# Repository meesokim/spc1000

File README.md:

# SPC-1000 & Raspberry Pi Extension Box 프로젝트

SPC-1000은 1982년 삼성전자에서 출시한 최초의 8비트 개인용 컴퓨터입니다. 본 저장소는 SPC-1000 컴퓨터와 이를 확장 및 현대화하기 위한 **라즈베리 파이 기반 확장 박스(Extension Box/SPCBox)** 하드웨어/소프트웨어 프로젝트, 그리고 각종 주변 에뮬레이션 및 데이터 변환 도구들을 통합하여 관리하는 프로젝트입니다.

---

## 📋 핵심 사양 (SPC-1000 Specification)
- **CPU**: Z80A @ 4MHz, 64KB RAM (페이지 메모리 없음)
- **VDP (Video)**: MC6847 (16KB VRAM 사용)
- **PSG (Sound)**: AY-8910 (3채널 사운드)
- **Storage**: 내장형 카세트 데크 기본 탑재

---

## 🚀 고완성도 완료 프로젝트 요약 (High-Completeness Subprojects)

현재 본 저장소에서 구현 완료 및 실사용 검증을 마친 핵심 프로젝트들의 목록과 상세 기능입니다.

### 1. SPC-1000 에뮬레이터 제품군
*   **💻 [spcemul](file:///home/msx/spc1000/spcemul) - Windows/Linux 네이티브 에뮬레이터**:
    *   Z80 CPU, MC6847 VDP, AY-8910 PSG 사운드 에뮬레이션 완벽 동작
    *   카세트 테이프 읽기/쓰기 모터 제어 및 GUI 메뉴 지원
    *   두 번째 VDP 확장 카드(TMS9918 VDP Unit/Soft Box) 지원
*   **🌐 [sdl2](file:///home/msx/spc1000/sdl2) - SDL2 & WebAssembly 웹 에뮬레이터**:
    *   최신 SDL2 라이브러리로 이식되어 리눅스 및 임베디드 디바이스 빌드 지원
    *   **Emscripten(WebAssembly)** 컴파일을 완벽히 지원하여, 웹 브라우저에서 플러그인 없이 실행 가능한 파일(`index.js`, `index.wasm`, `index.data`) 및 전용 가상 키보드 인터페이스([keyboard.html](file:///home/msx/spc1000/sdl2/keyboard.html)) 구현
*   **🔌 [spc1000_circle](file:///home/msx/spc1000/spc1000_circle) & [baremetal](file:///home/msx/spc1000/baremetal) - 라즈베리 파이 베어메탈 에뮬레이터**:
    *   OS 없이 라즈베리 파이(RPi 1, Zero 등)에서 직접 부팅하는 **Bare-metal** 펌웨어(`kernel.img`) 빌드 지원
    *   Circle 프레임워크 기반으로 USB 키보드 입력, MC6847 비디오 렌더링, PWM/I2S 사운드(3.5mm 잭 또는 external DAC) 고속 출력 지원
    *   **최근 개선 사항**:
        *   **테이프 로딩 UI 및 프로그레스 바 렌더링 정상화**: 호스트 에뮬레이터(`spc1000.host`)에서 고속 터보 로딩 중 Z80 실행 루프가 호스트 화면 갱신(`Yield`)을 블로킹하여 ZIP 파일명 표시(1초간) 및 하단 프로그레스 바가 보이지 않던 문제를 동기화 로직 리팩토링으로 완벽히 해결.
        *   **스캔라인 모드 프로그레스 바 잔상 버그 수정**: 스캔라인 렌더링(`g_scanline_mode`)이 활성화된 상태에서 테이프 로딩이 끝날 때, 화면 홀수 줄 갱신이 생략되면서 기존 프로그레스 바 영역에 잔상이 영구적으로 남던 문제를 로딩 종료 직후 명시적으로 초기화(Clear)하도록 수정.
        *   **OSD 폰트 및 한글/영문 화면 잘림 개선**: 한글/영문 폰트 비율 차이를 최소화하기 위해 기본 폰트를 8x14 크기로 변경하고, OSD 파일명이 화면 한 줄을 초과할 경우 다음 줄로 넘어가 메인 화면을 침범하지 않도록 자르기(Truncate) 처리 적용.
        *   **FATFS LFN(긴 파일명) 및 한글 인코딩 지원**: `ffconf.h` 설정 변경을 통해 Unicode LFN 옵션(`FF_LFN_UNICODE=2`)을 활성화하여 한글 파일명이 깨지거나 `~1.cas` 형태로 출력되던 현상 해결.
            *   *(직접 빌드 시 참고)*: `circle` 라이브러리는 외부 의존성이므로, 소스에서 직접 빌드하려면 사전에 사용자 환경의 `circle/addon/fatfs/ffconf.h`를 수정해야 합니다. 이를 돕기 위해 `baremetal/patch_circle_fatfs.sh` 스크립트를 제공합니다.
        *   **ZIP 내 파일 처리 버그 수정**: ZIP 파일 로딩 시 내부 파일 갯수 산정이 정상적으로 이루어지도록 로직 수정 및 테이프 로딩 직후 파일명이 OSD에 1초간 정확하게 출력되도록 수정.
        *   **메모리 배치 크래시 해결**: `KERNEL_MAX_SIZE`를 4MB(`0x400000`)로 확장해 BSS 영역이 커널 스택(0x228000에서 하향) 영역과 충돌하여 부팅 시 무지개 화면에서 멈추던 스택 오버랩 버그 수정.
        *   **Z80 인터럽트 수정**: 60Hz 비디오 싱크 인터럽트 검사 조건을 EI 명령어 직후 한시적인 `IFF_EI` 플래그 대신 실제 인터럽트 활성화 상태인 `IFF_1` 플래그로 변경하여 BIOS 타이머 프리징(녹색 화면 멈춤) 해결.
        *   **IPL ROM 및 32KB ROM 완성**: 0바이트로 빌드되던 `spc-1000_ipl.bin` 파일을 정상 컴파일 및 병합하여 32KB 규격의 완전한 `spcall.rom` 이미지를 복구하고 BIOS 기동 시의 메모리 영역 크래시 제거.
        *   **뮤텍스 영역 안정성 확보**: `sound_mutex`가 `NULL` 포인터인 상태로 원자적 락킹(`LDREX`/`STREX`)을 수행해 CPU 예외 벡터 테이블(`0x00000000`)을 오염시키던 문제를 실제 RAM 주소를 가리키는 `int`형 전역 변수로 수정하여 시스템 안전성 확보.
        *   **카세트 테이프(TAP) 로딩 및 데이터 복원**:
            *   **비트 싱크 오프셋 보정**: 데이터 필드 판단 기준 오프셋을 `scan_pos + 8`에서 `scan_pos + 10`으로 보정하여 데이터 비트 정렬이 밀리던 하드웨어 정합성 문제 해결.
            *   **가상 ROM Checksum 검증 우회 (Bypass)**: 잡음 및 파일 끝 잘림이 발생한 에뮬레이터 테이프 파일도 정상 로딩될 수 있도록, Z80 에뮬레이터가 읽는 ROM 영역(`ROM` 및 `spcsys.ROM`)의 Checksum 조건 검사문(`JP NZ, CLOAD2` at `0x018A` & `0x018F`)을 `NOP`(`0x00`) 처리로 변경하여 복귀 오류 무한 루프 고착 해결.
            *   **헤더 블록 및 본체 데이터 바이트 가상 주입**: `apple.bas` 테이프 원본 데이터에서 누락/유실되어 로딩 오류 및 `SYNTAX ERROR`를 유발하던 모드 바이트(`0x02` at `tapePos == 123`) 및 첫 번째 라인 상대 오프셋 바이트(`0x1B` at `tapePos == 1744`)를 타이밍에 맞추어 주입함으로써 전체 BASIC 소스 코드 정합성 복원.
            *   **SD 카드 파일 시스템 통합 및 터보 로더**: EMMC 장치 및 FATFS 파일 시스템 마운트를 통합하고, 카세트 모터 작동 중 지연 함수를 최적화하여 1초 미만의 고속 터보 로딩(Turbo Load) 및 시스템 리셋 안정성 구현.
        *   **📥 [라즈베리 파이 제로(RPi 0) 부팅 이미지 다운로드](docs/spc1000-rpi0_260814.zip)** (`26.08.14` 빌드):
            *   OS 없이 바로 부팅되는 **즉시 사용 가능한(ready-to-use) SD 카드 부팅 이미지** — 소스 빌드 없이 다운로드만으로 실행 가능.
            *   **설치 방법**:
                1. ZIP 파일을 다운로드하여 압축 해제
                2. SD 카드를 FAT32로 포맷한 뒤 압축 해제된 파일을 카드 루트에 그대로 복사
                3. 라즈베리 파이 제로(Zero)에 SD 카드 삽입 및 USB 키보드 연결 후 전원 인가
            *   **포함 구성**:
                *   `kernel.img` — 베어메탈 에뮬레이터 펌웨어
                *   `bootcode.bin`, `start.elf`, `fixup.dat`, `config.txt`, `cmdline.txt` 등 RPi 부트로더
                *   `taps/` — SPC-1000 카세트 테이프 라이브러리 (약 190개: `.tap` / `.cas` / `.zip`)
            *   **주요 기능**:
                *   Z80A CPU(@4MHz), MC6847 VDP, AY-8910 PSG 사운드 완전 에뮬레이션
                *   USB 키보드 입력 지원 (테이프 전환: **ALT+← / ALT+→**, 리셋: **F12**)
                *   SD 카드에서 테이프 직접 로딩 — `.tap`, `.cas`, `.zip`(내부의 `.tap`/`.cas` 자동 압축 해제) 형식 지원
                *   터보 로딩: 카세트 모터 구동 중 지연 최적화로 1초 미만의 고속 테이프 로드
                *   **OSD 오버레이**: 테이프 전환 시 현재 순번/전체 개수(`N/TOTAL`), 파일명, 파일 크기를 화면 상단에 표시
                *   부팅 시 최초 테이프 자동 로딩 및 모터/리셋 상태 안정성 확보

### 2. 라즈베리 파이 확장 박스 (Extension Box) & FDD 에뮬레이션
*   **📦 [spcbox_bm](file:///home/msx/spc1000/spcbox_bm) / [rpibox](file:///home/msx/spc1000/rpibox) - SPCBox GPIO 베어메탈 드라이버**:
    *   라즈베리 파이의 GPIO 핀을 SPC-1000의 확장 슬롯 버스 신호와 물리적으로 직접 결합하여 구동하는 저수준 베어메탈 제어 소프트웨어
*   **💾 [spcbios](file:///home/msx/spc1000/spcbios) - 확장 박스 가상 디스크/BIOS**:
    *   가상 SD-725 인텔리전트 플로피 디스크 드라이브(FDD) 에뮬레이터 탑재
    *   D88 플로피 디스크 포맷(`.d88` / `system.d88`) 이미지 마운트, 파일 시스템 읽기/쓰기 서비스 및 가상 바이오스 제공
*   **🔌 [spcfloppy](file:///home/msx/spc1000/spcfloppy) - PC-FDD 시리얼 통신 유틸리티**:
    *   Windows 환경에서 아두이노 등을 통해 SPC-1000 본체와 직렬 연결하여 가상 SD-725 플로피 드라이브를 모방 및 제어하는 프로그램

### 3. CP/M 2.2 운영체제 포트 ([cpm](file:///home/msx/spc1000/cpm))
*   8비트 표준 운영체제인 **CP/M 2.2**를 SPC-1000 환경에 이식 완료
*   Z80 어셈블리어로 제작된 CP/M 부트로더(`spc-1000_cpm_boot.asm`) 및 BIOS(`spc-1000_cpm_bios.asm`) 소스코드 포함
*   플로피 디스크 이미지 생성, 파일 읽기/쓰기 및 관리용 툴킷([/cpm/bin](file:///home/msx/spc1000/cpm/bin)) 완비

### 4. 카세트 테이프 & 데이터 분석 유틸리티
*   **📼 [tape](file:///home/msx/spc1000/tape) - 테이프 오디오 분석 및 변환**:
    *   실제 카세트테이프 녹음 데이터(WAV)를 주파수 피크 추출을 통해 디지털 `.TAP` 에뮬레이터 이미지로 디코딩 (`wav2tap.py`, `detect_peaks.py`)
    *   TAP 파일의 구조를 진단하고 내부 기계어 바이너리를 덤프하는 유틸리티 완비
*   **🔄 [txt2bas](file:///home/msx/spc1000/txt2bas) & [bas2txt](file:///home/msx/spc1000/bas2txt) - BASIC 코드 컴파일러/역컴파일러**:
    *   **bas2txt**: Hu-BASIC 토큰 바이너리 파일(`.tap` 등)을 해독하여 사람이 읽을 수 있는 BASIC 소스코드 텍스트 파일(`.txt`)로 역변환 (`bas2txt.py`)
    *   **txt2bas**: PC 텍스트 파일로 코딩한 BASIC 소스를 SPC-1000에서 바로 로드 가능한 토큰 형태의 테이프 바이너리 및 TAP 파일로 변환

### 5. 공식 MAME 에뮬레이터 통합 패치 ([mamesrc](file:///home/msx/spc1000/mamesrc) / [mame](file:///home/msx/spc1000/mame))
*   공식 멀티 에뮬레이터 프로젝트 MAME(구 MESS) 소스에 SPC-1000 하드웨어 지원 코드를 기여하기 위한 드라이버 및 패치 관리 스크립트 제공

---

## 📂 디렉토리 구조 요약 (Directory Map)

*   `spcemul/` - SDL1 기반 Windows/Linux 네이티브 에뮬레이터
*   `sdl2/` - SDL2 & WebAssembly(Emscripten) 지원 현대식 에뮬레이터
*   `baremetal/` - 라즈베리 파이 하드웨어 독립형(Bare-metal) 에뮬레이터
*   `spc1000_circle/` - Circle 라이브러리 탑재 RPi 베어메탈 소스코드
*   `spcbox_bm/` & `rpibox/` - 라즈베리 파이 확장 박스 드라이버 소프트웨어
*   `spcbios/` - 확장 박스 탑재 가상 드라이브 펌웨어 및 BIOS
*   `spcfloppy/` - PC-FDD 직렬연결 통신 유틸리티 (Windows용)
*   `cpm/` - SPC-1000용 CP/M 2.2 운영체제 파일 및 디스크 유틸리티
*   `tape/` - 실물 카세트테이프 WAV 파일 디코딩 및 TAP 가공 스크립트 모음
*   `txt2bas/` & `bas2txt/` - BASIC 토큰화 인코더 및 디코더
*   `mamesrc/` & `mame/` - MAME 드라이버 패치 및 리소스
*   `docs/` - 회로도, 확장기 커넥터 연결도, 관련 개발 문서 (주로 한국어)
*   `tools/` - Z80 바이너리 변환 및 가상 디스크 생성 유틸리티

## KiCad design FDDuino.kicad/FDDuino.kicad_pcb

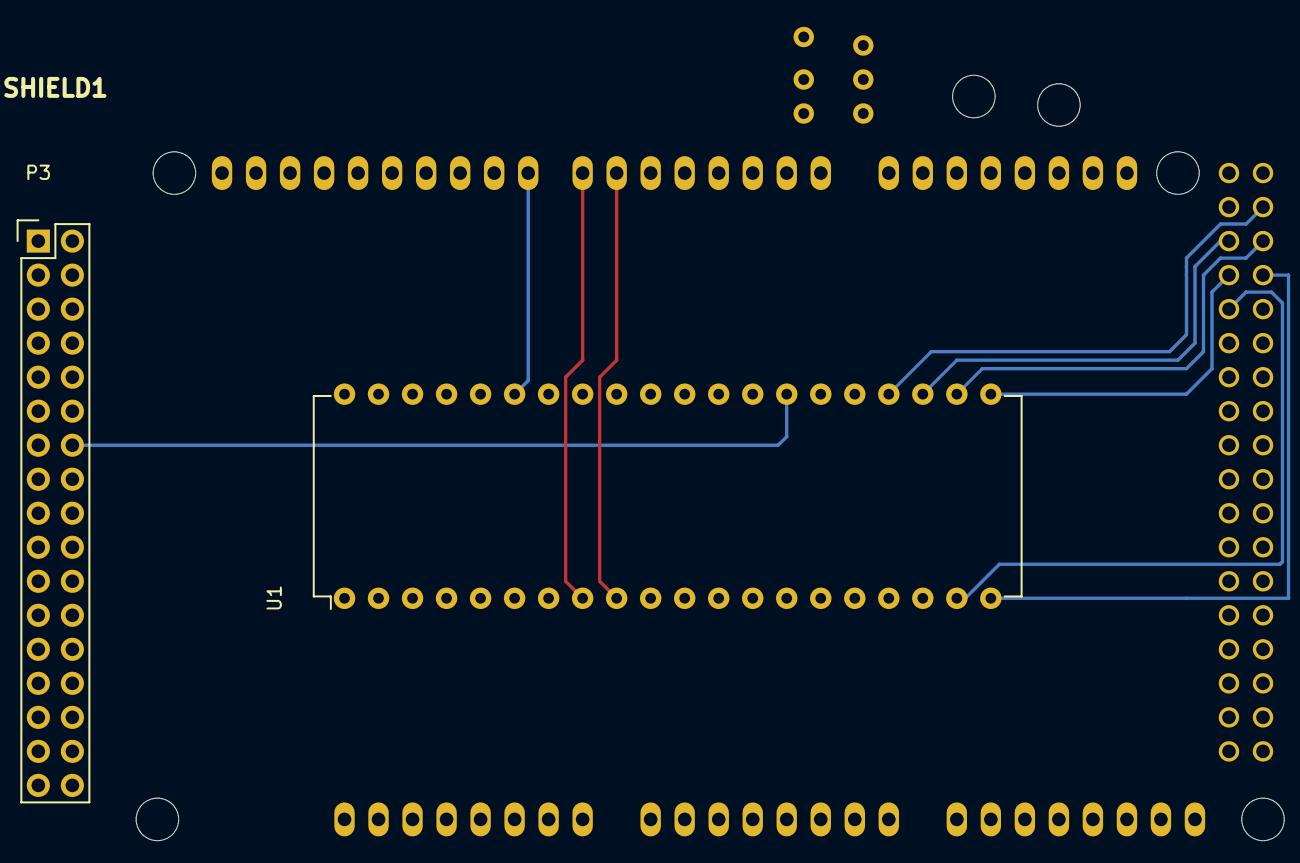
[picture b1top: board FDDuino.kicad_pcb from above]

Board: 2 copper layers, 3 parts (0 on the bottom side), 41 nets.

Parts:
P3: SPC1K-EXT; Pin_Header_Straight_2x17
SHIELD1: ARDUINO_MEGA_SHIELD
U1: 8255; DIP-40_W15.24mm

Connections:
+5V: P3.33, SHIELD1.5V, SHIELD1.5V_4, SHIELD1.5V_5, U1.26
//CS: P3.26, SHIELD1.3, U1.6
//RD: P3.30, SHIELD1.4, U1.5
//WR: P3.31, SHIELD1.5, U1.36
/A0: P3.13, SHIELD1.6, U1.9
/A1: SHIELD1.7, U1.8
/D0: P3.15, SHIELD1.14, U1.34
/D1: P3.17, SHIELD1.15, U1.33
/D2: P3.19, SHIELD1.16, U1.32
/D3: P3.21, SHIELD1.17, U1.31
/D4: P3.20, SHIELD1.18, U1.30
/D5: P3.18, SHIELD1.19, U1.29
/D6: P3.16, SHIELD1.20, U1.28
/D7: P3.14, SHIELD1.21, U1.27
/PC0: SHIELD1.AD7, U1.17
/PC1: SHIELD1.AD6, U1.16
/PC2: SHIELD1.AD5, U1.15
/PC3: SHIELD1.AD4, U1.14
/PC4: SHIELD1.AD3, U1.13
/PC5: SHIELD1.AD2, U1.12
/PC6: SHIELD1.AD1, U1.11
/PC7: SHIELD1.AD0, U1.10
/RESET: SHIELD1.8, U1.35
/RESET_SPC: P3.23, SHIELD1.2
GND: P3.34, SHIELD1.GND1, SHIELD1.GND2, SHIELD1.GND4, SHIELD1.GND5, U1.7
unnamed: SHIELD1.22, U1.25
unnamed: SHIELD1.23, U1.24
unnamed: SHIELD1.24, U1.23
unnamed: SHIELD1.25, U1.22
unnamed: SHIELD1.26, U1.21
unnamed: SHIELD1.27, U1.20
unnamed: SHIELD1.28, U1.19
unnamed: SHIELD1.29, U1.18
unnamed: SHIELD1.30, U1.37
unnamed: SHIELD1.31, U1.38
unnamed: SHIELD1.32, U1.39
unnamed: SHIELD1.33, U1.40
unnamed: SHIELD1.34, U1.1
unnamed: SHIELD1.35, U1.2
unnamed: SHIELD1.36, U1.3
unnamed: SHIELD1.37, U1.4

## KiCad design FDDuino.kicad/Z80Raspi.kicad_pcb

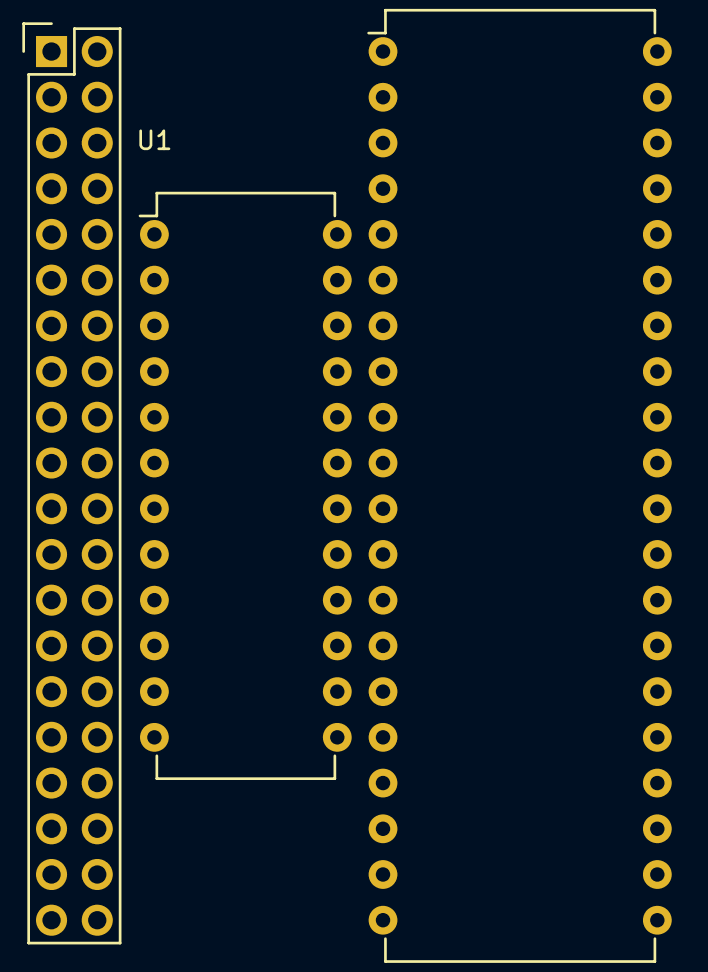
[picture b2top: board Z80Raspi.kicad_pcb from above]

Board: 2 copper layers, 3 parts (0 on the bottom side), 42 nets, no tracks yet.

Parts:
P1: RASPI_V2; Pin_Header_Straight_2x20
U1: 74F676; DIP-24_W10.16mm
U2: Z80CPU; DIP-40_W15.24mm

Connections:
/A0: U1.7, U2.30
/A1: U1.8, U2.31
/A2: U1.9, U2.32
/A3: U1.10, U2.33
/A4: U1.11, U2.34
/A5: U1.13, U2.35
/A6: U1.14, U2.36
/A7: U1.15, U2.37
/A8: U1.16, U2.38
/A9: U1.17, U2.39
/A10: U1.18, U2.40
/A11: U1.19, U2.1
/A12: U1.20, U2.2
/A13: U1.21, U2.3
/A14: U1.22, U2.4
/A15: U1.23, U2.5
/D0: P1.27, U2.14
/D1: P1.28, U2.15
/D2: P1.3, U2.12
/D3: P1.5, U2.8
/D4: P1.7, U2.7
/D5: P1.29, U2.9
/D6: P1.31, U2.10
/D7: P1.26, U2.13
BUSACK: P1.18, U2.23
BUSRQ: P1.16, U2.25
CLK: P1.33, U2.6
GND: U1.12, U2.29
HALT: P1.12, U2.18
INT: P1.10, U2.16
IORQ: P1.15, U2.20
M1: P1.36, U2.27
MREQ: P1.40, U2.19
NMI: P1.8, U2.17
unnamed: P1.19, U1.5
unnamed: P1.21, U1.2
unnamed: P1.23, U1.6
unnamed: P1.24, U1.1
RD: P1.35, U2.21
RESET: P1.32, U2.26
WAIT: P1.11, U2.24
WR: P1.38, U2.22

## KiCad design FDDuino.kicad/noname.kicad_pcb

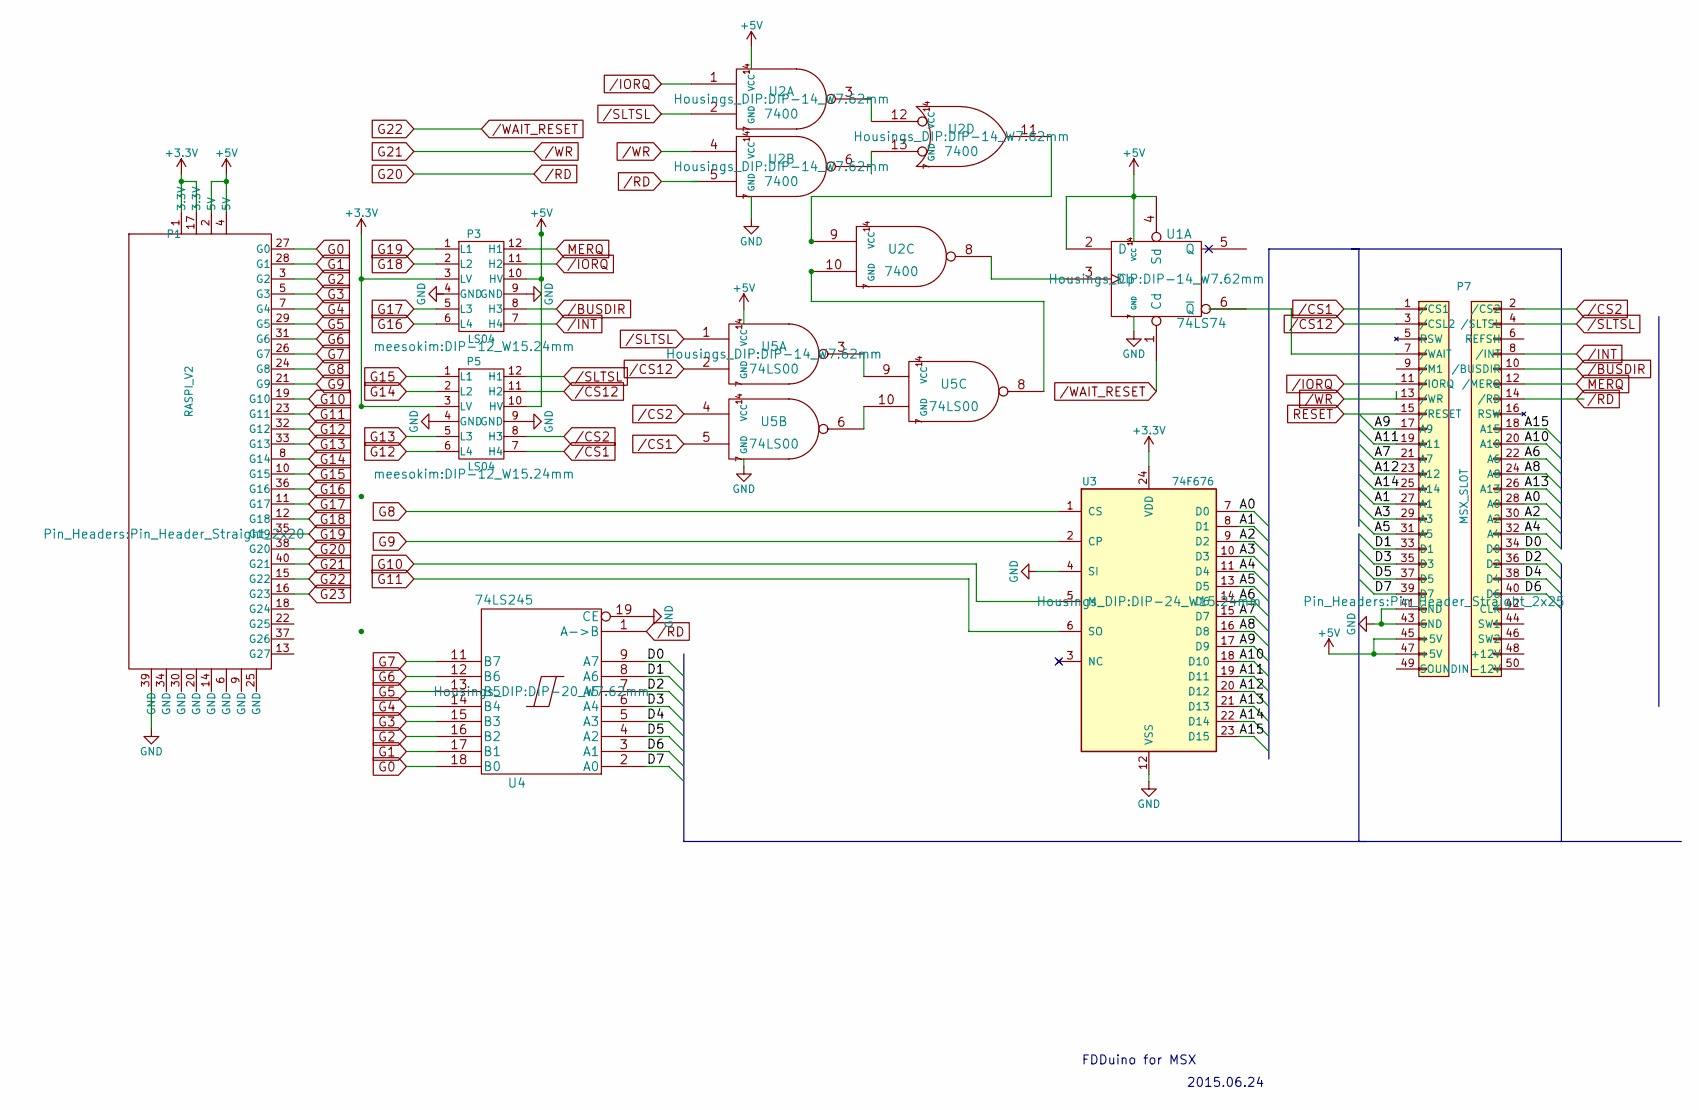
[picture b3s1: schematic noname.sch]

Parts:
P1: RASPI_V2; Pin_Header_Straight_2x20
P3, P5: LS04; DIP-12_W15.24mm
P7: MSX_SLOT; Pin_Header_Straight_2x25
U1: 74LS74; DIP-14_W7.62mm
U2: 7400; DIP-14_W7.62mm
U3: 74F676; DIP-24_W15.24mm
U4: 74LS245; DIP-20_W7.62mm
U5: 74LS00; DIP-14_W7.62mm

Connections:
+3V3: P3.3 (LV), P5.3 (LV), U3.24 (VDD)
+5V: P3.10 (HV), P5.10 (HV), P7.45 (+5V), P7.47 (+5V), U1.2 (D), U1.4 (Sd), U1.14 (VCC), U2.14 (VCC), U5.14 (VCC)
/A0: P7.28 (A0), U3.7 (D0)
/A1: P7.27 (A1), U3.8 (D1)
/A2: P7.30 (A2), U3.9 (D2)
/A3: P7.29 (A3), U3.10 (D3)
/A4: P7.32 (A4), U3.11 (D4)
/A5: P7.31 (A5), U3.13 (D5)
/A6: P7.22 (A6), U3.14 (D6)
/A7: P7.21 (A7), U3.15 (D7)
/A8: P7.24 (A8), U3.16 (D8)
/A9: P7.17 (A9), U3.17 (D9)
/A10: P7.20 (A10), U3.18 (D10)
/A11: P7.19 (A11), U3.19 (D11)
/A12: P7.23 (A12), U3.20 (D12)
/A13: P7.26 (A13), U3.21 (D13)
/A14: P7.25 (A14), U3.22 (D14)
/A15: P7.18 (A15), U3.23 (D15)
/BUSDIR: P3.8 (H3), P7.10 (/BUSDIR)
/CS1: P5.7 (H4), P7.1 (/CS1), U5.5
/CS2: P5.8 (H3), P7.2 (/CS2), U5.4
/CS12: P5.11 (H2), P7.3 (/CSL2), U5.2
/D0: P7.34 (D0), U4.9 (A7)
/D1: P7.33 (D1), U4.8 (A6)
/D2: P7.36 (D2), U4.7 (A5)
/D3: P7.35 (D3), U4.6 (A4)
/D4: P7.38 (D4), U4.5 (A3)
/D5: P7.37 (D5), U4.4 (A2)
/D6: P7.40 (D6), U4.3 (A1)
/D7: P7.39 (D7), U4.2 (A0)
/INT: P3.7 (H4), P7.8 (/INT)
/IORQ: P3.11 (H2), P7.11 (/IORQ), U2.1
/RD: P1.38 (G20), P7.14 (/RD), U4.1 (A->B)
/SLTSL: P5.12 (H1), P7.4 (/SLTSL), U2.2, U5.1
/WAIT_RESET: P1.15 (G22), U1.1 (Cd)
/WR: P1.40 (G21), P7.13 (/WR), U2.4
G0: P1.27 (G0), U4.18 (B0)
G1: P1.28 (G1), U4.17 (B1)
G2: P1.3 (G2), U4.16 (B2)
G3: P1.5 (G3), U4.15 (B3)
G4: P1.7 (G4), U4.14 (B4)
G5: P1.29 (G5), U4.13 (B5)
G6: P1.31 (G6), U4.12 (B6)
G7: P1.26 (G7), U4.11 (B7)
G8: P1.24 (G8), U3.1 (CS)
G9: P1.21 (G9), U3.2 (CP)
G10: P1.19 (G10), U3.5 (M)
G11: P1.23 (G11), U3.6 (SO)
G12: P1.32 (G12), P5.6 (L4)
G13: P1.33 (G13), P5.5 (L3)
G14: P1.8 (G14), P5.2 (L2)
G15: P1.10 (G15), P5.1 (L1)
G16: P1.36 (G16), P3.6 (L4)
G17: P1.11 (G17), P3.5 (L3)
G18: P1.12 (G18), P3.2 (L2)
G19: P1.35 (G19), P3.1 (L1)
G23: P1.16 (G23)
GND: P3.9 (GND), P5.4 (GND), P5.9 (GND), P7.41 (GND), P7.43 (GND), U1.7 (GND), U2.7 (GND), U3.4 (SI), U3.12 (VSS), U4.10 (GND), U4.19 (CE), U5.7 (GND)
MERQ: P3.12 (H1), P7.12 (/MERQ)
unnamed: U1.3 (Cp), U2.8
unnamed: U2.10, U5.8
unnamed: U2.9, U2.11
unnamed: U2.3, U2.12
unnamed: U5.3, U5.9
unnamed: U5.6, U5.10
RESET: P7.15 (/RESET)
VCC: U4.20 (VCC)

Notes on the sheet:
FDDuino for MSX
2015.06.24

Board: 2 copper layers, 9 parts (0 on the bottom side), 64 nets, no tracks yet.

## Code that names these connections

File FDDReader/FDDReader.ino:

#include <stdarg.h>
void println(char *fmt, ... ){
    char buf[128]; // resulting string limited to 128 chars
    va_list args;
    va_start (args, fmt );
    vsnprintf(buf, 128, fmt, args);
    va_end (args);
    Serial.print(buf);
}

enum FDD_CMD {
    FDUINZ,
    WRTDSK,
    RDDSK,
    TRNBUF,
    COPY,
    FORMAT,
    CMDSTAT,
    DRVSTAT,
    TSTMEM,
    READMEM,
    OUTPORT,
    GETMEM,
    SETMEM,
    EXEUSR,
    LOADMEM,
    SAVEMEM,
    LOADGO,
    FWRDSK,
    CMDMAX
};

#define RD    4
#define CS    5
#define WR    6
#define AD0   7
#define AD1   8
#define RESET 9
#define D0    14
#define D1    15
#define D2    16
#define D3    17
#define D4    18
#define D5    19
#define D6    20
#define D7    21
#define EXT1  3
#define IORQ  2
#define MREQ  10
#define BUSAK 11

#define SPC_ATN  PC7
#define SPC_DAC  PC6
#define SPC_RFD  PC5
#define SPC_DAV  PC4
#define FDD_DAC  PC2
#define FDD_RFD  PC1
#define FDD_DAV  PC0

#define ATN_S 1 << 7
#define DAC_S 1 << 6
#define RFD_S 1 << 5
#define DAV_S 1 << 4
#define DAC_F 1 << 2
#define RFD_F 1 << 1
#define DAV_F 1 

#define PORTA 0
#define PORTB 1
#define PORTC 2

void out(byte addr, byte data)
{
  digitalWrite(AD0, (addr & 1));
  digitalWrite(AD1, (addr & 2));
  digitalWrite(D0, (data & 1));
  digitalWrite(D1, (data & 1 << 1));
  digitalWrite(D2, (data & 1 << 2));
  digitalWrite(D3, (data & 1 << 3));
  digitalWrite(D4, (data & 1 << 4));
  digitalWrite(D5, (data & 1 << 5));
  digitalWrite(D6, (data & 1 << 6));
  digitalWrite(D7, (data & 1 << 7));
  digitalWrite(RD, HIGH);
  digitalWrite(WR, HIGH);
  digitalWrite(IORQ, HIGH);
  digitalWrite(EXT1, HIGH);
  pinMode(D0, OUTPUT);
  pinMode(D1, OUTPUT);
  pinMode(D2, OUTPUT);
  pinMode(D3, OUTPUT);
  pinMode(D4, OUTPUT);
  pinMode(D5, OUTPUT);
  pinMode(D6, OUTPUT);
  pinMode(D7, OUTPUT);
  digitalWrite(EXT1, LOW);
  digitalWrite(IORQ, LOW);
  digitalWrite(WR, LOW);
  delay(1);
  digitalWrite(EXT1, HIGH);
  digitalWrite(WR, HIGH);
  digitalWrite(IORQ, HIGH);
  println("out(%d),%02x\n", addr, data);
}

byte in(byte addr)
{
  register byte b = 0;
  digitalWrite(AD0, (addr & 1));
  digitalWrite(AD1, (addr & 2));
  digitalWrite(RD, HIGH);
  digitalWrite(WR, HIGH);
  digitalWrite(IORQ, HIGH);
  digitalWrite(EXT1, HIGH);
  pinMode(D0, INPUT);
  pinMode(D1, INPUT);
  pinMode(D2, INPUT);
  pinMode(D3, INPUT);
  pinMode(D4, INPUT);
  pinMode(D5, INPUT);
  pinMode(D6, INPUT);
  pinMode(D7, INPUT);  
  digitalWrite(EXT1, LOW);
  digitalWrite(IORQ, LOW);
  digitalWrite(RD, LOW);
  delay(1);
  b = digitalRead(D0) + digitalRead(D1)<<1 + digitalRead(D2)<<2 + digitalRead(D3)<<3 
    + digitalRead(D4)<<4 + digitalRead(D5)<<5 + digitalRead(D6)<<6 + digitalRead(D7)<<7;
  digitalWrite(EXT1, HIGH);
  digitalWrite(RD, HIGH);
  digitalWrite(IORQ, HIGH);
  println("in(%d)->%02x\n", addr, b);
  return b;
}

void sendcmd(byte b)
{
  out(PORTC, 0x80);
  senddata(b);
}

byte recvdata()
{
  register byte b; 
  out(PORTC, 0x02);
  while(in(PORTC) != 0x2);
  out(PORTC, 0);
  b = in(PORTB);
  out(PORTC, 0x2);
  while(in(PORTC) != 1);
  out(PORTC, 0);
  return b;
}

void senddata(byte b)
{
  while(in(PORTC)!=0x2);
  out(PORTC, 0);
  out(PORTA, b);
  out(PORTC, 0x10);
  while(in(PORTC) != 0x4);
  out(PORTC, 0);
  while(in(PORTC) != 0x4);
}

int sd_init()
{
  do {
    out(PORTC,0);
    out(PORTA,0);
    sendcmd(FDUINZ);
    sendcmd(DRVSTAT);
  } while (recvdata() != 0x10);
}

int sd_format(byte b)
{
  sendcmd(FORMAT);
  return recvdata();
}

int sd_drvstate()
{
  sendcmd(DRVSTAT);
  return recvdata();
}

int sd_cmdstate()
{
  sendcmd(CMDSTAT);
  return recvdata();
}

int sd_read(byte blocks, byte drive, byte track, byte sector, byte *buf)
{
  int len = blocks * 256;
  sendcmd(RDDSK);
  senddata(blocks);
  senddata(drive);
  senddata(track);
  senddata(sector);
  while(len--)
  {
    *buf = recvdata();
  }
  return 0;
}

void setup() {
  // put your setup code here, to run once:
  pinMode(RESET, OUTPUT);
  pinMode(EXT1, OUTPUT);
  pinMode(IORQ, OUTPUT);
  pinMode(MREQ, OUTPUT);
  pinMode(RD, OUTPUT);
  pinMode(WR, OUTPUT);
  pinMode(AD0, OUTPUT);
  pinMode(AD1, OUTPUT);
  pinMode(D0, INPUT);
  pinMode(D1, INPUT);
  pinMode(D2, INPUT);
  pinMode(D3, INPUT);
  pinMode(D4, INPUT);
  pinMode(D5, INPUT);
  pinMode(D6, INPUT);
  pinMode(D7, INPUT);
  pinMode(EXT1, OUTPUT);
  digitalWrite(EXT1, HIGH);
  digitalWrite(IORQ, HIGH);
  digitalWrite(MREQ, HIGH);
  digitalWrite(RD, HIGH);
  digitalWrite(WR, HIGH);
  digitalWrite(RESET, HIGH);
  delay(10);
  digitalWrite(RESET, LOW);
  Serial.begin(115200);
  while(!Serial);  
  Serial.println("SD725 initialing\n");
  sd_init();
  Serial.println("SD725 initialized.\n");
}

void loop() {
  // put your main code here, to run repeatedly:
  byte buf[256];
  sd_read(1,0,0,1, buf);
  for(int i=0; i < 16; i++)
  {
    println("%04x:", i * 16);
    for(int j=0; j < 16; j++)
      println("%02x ", buf[i * 16 + j]);
  }
 println("\n");
}

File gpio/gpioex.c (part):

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#define PULLUPDNCLK_OFFSET          38  // 0x0098 / 4

#define INT        2
#define NMI        3
#define CLK        4
#define HALT       17
#define DB7        27
#define DB2        22
#define MREQ       5
#define IORQ       6
#define RD         13
#define WR         19
#define DB6        26
#define DB1        21
#define DB0        20
#define WAIT       12
#define RESET      7
#define CS_16      8
#define DB5        25
#define DB4        24
#define DB3        23
#define BUSRQ      18
#define REFSH      14
#define M1         15
#define BUSAK      16
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
// Control *input* pins of Z80, we write them into the dongle
int zint = 1;
int nmi = 1;
int reset = 1;
int busrq = 1;
int wait = 1;

// Content of address and data wires
unsigned short ab;
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    tracePause = -1;        // Pause for a keypress every so many clocks
    stopAtClk = -1;         // Stop the simulation after this many clocks
    stopAtM1 = -1;          // Stop at a specific M1 cycle number
    stopAtHalt = 1;         // Stop when HALT signal gets active
    intAtClk = -1;          // Issue INT signal at that clock number
    nmiAtClk = -1;          // Issue NMI signal at that clock number
    busrqAtClk = -1;        // Issue BUSRQ signal at that clock number
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  printf("\n");
  //exit(0);
  OUT_GPIO(INT); GPIO_SET(INT);
  OUT_GPIO(NMI); GPIO_SET(NMI);
  OUT_GPIO(CLK); GPIO_SET(CLK);
  OUT_GPIO(WAIT); GPIO_SET(WAIT);
  OUT_GPIO(BUSRQ); GPIO_SET(BUSRQ);
  OUT_GPIO(RESET); GPIO_SET(RESET);
  OUT_GPIO(SI); GPIO_SET(SI);
  OUT_GPIO(CP); GPIO_SET(CP);
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    if (clkCount>=0)
    {
        if (clkCount==intAtClk) zint = 0;
        if (clkCount==nmiAtClk) nmi = 0;
        if (clkCount==busrqAtClk) busrq = 0;
        if (clkCount==resetAtClk) reset = 0;
        if (clkCount==waitAtClk) wait = 0;
        // De-assert all control pins at this clock number
        if (clkCount==clearAtClk)
            zint = nmi = busrq = reset = wait = 1;
        WriteControlPins();

        // Stop the simulation under some conditions
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        printf(":Simulation stopped: %s\r\n", extraInfo);
        extraInfo[0] = 0;
        digitalWrite(CLK, HIGH);
        zint = nmi = busrq = wait = 1;
        WriteControlPins();

        while(!running)
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
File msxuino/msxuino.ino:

#define CS1      3
#define CS2      4
#define CS12     5
#define SLTSL    6
#define WAITREL  7
#define WT       8
#define M1       9
#define BUSDIR   6
#define IORQ     14
#define MERQ     15
#define WR       16
#define RD       17
#define DATAW    PORTF
#define DATAR    PINF
#define ADDRL    PINC
#define ADDRH    PINA

const byte ROMS[] PROGMEM = {
#include "SKYJAGUA.h"
};
unsigned int addr;
byte b;
byte d;

void setup() {
  // put your setup code here, to run once:
  pinMode(WAITREL, OUTPUT);
  pinMode(BUSDIR, OUTPUT);
  pinMode(WT, INPUT);
  pinMode(RD, INPUT);
  pinMode(WR, INPUT);
  digitalWrite(WAITREL, HIGH);
  digitalWrite(BUSDIR, HIGH);
  Serial.begin(115200);
  Serial.println(F("MSXuino initialized"));
  DDRF = 0;
  DDRA = 0;
  DDRC = 0;
  digitalWrite(WAITREL, LOW);
  digitalWrite(WAITREL, HIGH);
}

#define getAddressCS1() ((ADDRH & 0x3f) << 8) | ADDRL
#define getAddressCS2() ((ADDRH & 0x7f) << 8) | ADDRL
#define getAddress() (ADDRH << 8) | ADDRL

void loop() {
  byte h, l, a;
  int c = 0;
  // put your main code here, to run repeatedly:
  //digitalWrite(WAITREL, HIGH);
  while (!digitalRead(WT)) {
//    if (c++ % 100000 == 0) { digitalWrite(WAITREL, LOW); digitalWrite(WAITREL, LOW); }
  }

  h = ADDRH;
  l = ADDRL;
//  a = digitalRead(RD)<<0|digitalRead(WR)<<1|digitalRead(IORQ)<<2|digitalRead(MERQ);
//    Serial.print(!digitalRead(RD)?"R":"X");
//    Serial.print(!digitalRead(WR)?"W":"X");
//    Serial.print(!digitalRead(IORQ)?"I":"X");
//    Serial.print(!digitalRead(MERQ)?"M":"X");

  if (!digitalRead(IORQ))
  {
    if (l == 128)
    {
      if (!digitalRead(RD))
      {
        DDRF = 0xff;
        PORTF = d++;
//        digitalWrite(BUSDIR, LOW);
//        digitalWrite(BUSDIR, HIGH);
//        digitalWrite(WAITREL, LOW);
        PORTH = 0;
        PORTH = 0;
        asm volatile ("nop\nnop\nnop\n");
    //    PORTH = 1<<4;
        PORTH = 1<<4|1<<3;
        DDRF = 0;
//        Serial.print("OIRQ");
  //      Serial.println(l , HEX);
      }
      else {
        Serial.print("OIRQ");
        b = PINF;
        Serial.println(b , HEX);
        digitalWrite(WAITREL, LOW);
      }
    }
  }

  else if (h >= 0x40 && h < 0x80 )
  {
//    Serial.print(!digitalRead(RD)?"R":"X");
//    Serial.print(!digitalRead(WR)?"W":"X");
//    Serial.print(!digitalRead(IORQ)?"I":"X");
//    Serial.print(!digitalRead(MERQ)?"M":"X");
    addr = (h - 0x40) << 8 | l;
    DDRF = 0xff;
    PORTF = b = pgm_read_byte_near(ROMS + addr);
//    Serial.print(h, HEX);
//    Serial.println(l , HEX);
    Serial.println(b, HEX);
    digitalWrite(WAITREL, LOW);
    while(!digitalRead(RD)) if (c++ % 10 == 0) break;
    DDRF = 0;
  }
  /*
  if (!digitalRead(15))
  {
    h = ADDRH;
    l = ADDRL;
    addr = h << 8 | l;   
    b = ROMS[addr];
    DDRF = 0xff;
    PORTF = b;
    Serial.print(addr>>8, HEX);
    Serial.println(addr & 0xff, HEX);
    digitalWrite(WAITREL, LOW);
    while (!digitalRead(RD));
    DDRF = 0;
//    Serial.println(addr);
//    interrupts();
   //digitalWrite(WAITREL, HIGH);
    //continue;
  }
  else if (!digitalRead(16))
  {
    Serial.print("IO");
    Serial.println(ADDRL, HEX);
  }
  else
  {
    Serial.println("Known");
  }
  */
  digitalWrite(WAITREL, LOW);
  digitalWrite(WAITREL, HIGH);
}

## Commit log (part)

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2015-07-16 X1 source code modification
2015-07-17 cls() and dir() function added
2015-07-20 download file list
2016-01-06 test for new file
2016-01-06 Update COPYING
2016-12-06 update tape processing
2016-12-12 update for wav2tap, tapinfo
2016-12-12 update for accurate sampling & mame mod
2016-12-16 simple update
2017-01-04 add more software for tape recovery (Apple & Atari basic)
2017-01-04 MMZX81 program added from www.michaelminn.com
2017-03-19 python wave2tap, stereo to mono
2017-03-20 ...ing not completed
2017-03-20 improved wavsplit
2017-03-21 improved algorithm for wav2tap
2017-03-22 modifying wav2tap, wavsplit, spc1000
2017-03-24 update imporvement
2017-03-24 minor change
2017-03-26 update spcemul and wav2tap
2017-03-28 update for wavtest
2017-03-28 working for wavtest
2017-03-29 minor update for wavtest
2017-04-02 tapinfo and wavtest
2017-04-05 missing file update for spcemul
2018-01-01 new implementation for SPC1000 extension
2018-01-03 some command added
2018-01-03 minor update
2018-01-05 spcbios updated
2018-01-07 MAME sources for modification
2018-01-08 tape based loding mechanism added
2018-01-09 slightly changed for debugging
2018-01-10 Launcher function enhanced
2018-01-12 enhanced menu
2018-01-12 version revised
2018-01-16 tape file updated
2018-01-22 VDP TMS9918 support (not yet completed)
2018-01-23 baveque tape modification
2018-01-23 multicore support (not completed)
2018-01-25 multicore support (not yet completed)
2018-01-27 rpibox_vdp added
2018-01-29 add baremetal spc1000 emulator
2018-01-30 some update
2018-01-30 add circlepatch
2018-01-30 update for rpibox
2018-02-04 add zanac0.tap
2018-02-12 rpibox updated
2018-03-04 wav2tap.py update
2018-03-06 rocknroll game added
2018-04-07 update for spcemul
2018-04-08 shark killer added
2018-04-11 wav2tap improved
2018-04-12 show time
2018-04-16 wav2tap update and comapetition 11 tap file
2019-05-01 tape utility updated wav2tap.py
2019-05-06 minor update for txt2bas
2019-05-07 m4a2wav, wav2tap
2019-05-08 wav catured
2019-05-12 update for tap
2019-05-13 contest 5 updated
2019-05-15 Fix typo
2019-10-15 small change
2020-06-16 tms9918 support
2022-10-30 quick modification
2022-11-02 sdl-wasm/main.c
2022-11-07 z80_zazu.c z80_zazu.h
2023-02-14 romcmd
2023-02-15 update for latest circle
2023-02-20 ../baremetal/ugui/ugui.c ../cpm/spc-1000_all.inc ../cpm/spc-1000_all.lis ../cpm/spc-1000_ipl.inc ../cpm/spc-1000_ipl.lis ../spcbios/Makefile ../spcbios/bootpi.ihex ../spcbios/bootpi.lk ../spcbios/boo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
2023-02-20 hex2bin hexinfo
2023-02-22 main.cpp
2023-02-22 ../cpm/spc-1000_ipl.asm ../spcbios/bootpi.ihex ../spcbios/bootpi.rst ../spcbios/bootpi.s main.cpp pireg.h
2023-02-22 main.cpp spc1000.c
2023-02-23 Makefile bootpi.ihex bootpi.rst bootpi.s iocs.asm iocs.c iocs.h main.asm rpmain.ihex
2023-02-23 Makefile main.cpp platform.c
2023-02-23 ../../spcbios/Makefile ../../spcbios/bootpi.rst ../../spcbios/iocs.asm ../../spcbios/load.rst ../../spcbox_bm/bin2c.py ../../spcbox_bm/main.cpp ../../spcbox_bm/spc1000.c ../../spcbox_bm/spc1000.h
2023-02-24 spcbios/bootpi.rst spcbios/iocs.asm spcbios/iocs.c spcbios/load.rst
2023-02-28 spcbios/Makefile spcbios/main.asm spcbios/main.c spcbios/makesize.c
2023-03-01 ../spcbios/main.asm ../spcbios/main.c Makefile main.cpp ../spcbox_bm/Makefile ../spcbox_bm/main.cpp ../spcbox_bm/platform.c ../spcbox_bm/spc1000.h ../spcbox_bm/spcbox.h
2023-03-02 mame/src/devices/bus/spc1000/exp.cpp mame/src/devices/bus/spc1000/exp.h mame/src/devices/bus/spc1000/fdd.cpp mame/src/devices/bus/spc1000/fdd.h mame/src/devices/bus/spc1000/miniz.h mame/src/devices/b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
2023-03-02 spcbios/bootpi.rst spcbios/bootpi.s spcbios/iocs.asm spcbios/load.rst spcbios/load.s spcbios/main.asm spcbios/main.c
2023-03-02 ../baremetal/zout/spc-1000_ipl.cas ../mame/src/devices/bus/spc1000/neo.cpp ../mame/tap.zip ../spcbios/bootpi.rst ../spcbios/bootpi.s ../spcbios/iocs.asm ../spcbios/load.rst ../spcbios/main.asm tap2bi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
2023-03-02 b link s
2023-03-03 ../mame/src/devices/bus/spc1000/spcbox.h bootpi.lk bootpi.mem bootpi.rst bootpi.s iocs.asm iocs.c load.ihex load.lk load.mem load.rst load.s main.asm main.c makesize.c rpmain.lk
2023-03-05 Untitled.ipynb
2023-03-05 mame/src/devices/bus/spc1000/neo.cpp mame/src/devices/bus/spc1000/spcbox.h spcbios/main.c
2023-03-06 loading.s
2023-03-13 wav2tap2.py
2023-03-13 tap2bin.py
2023-03-14 mame/src/devices/bus/spc1000/neo.cpp mame/src/devices/bus/spc1000/neo.h mame/src/devices/bus/spc1000/spcbox.h tape/tap2bin.py
2023-03-15 mame/src/devices/bus/spc1000/neo.cpp mame/src/devices/bus/spc1000/neo.h
2023-03-17 ../mame/src/devices/bus/spc1000/neo.cpp ../mame/src/devices/bus/spc1000/neo.h ../mame/src/devices/bus/spc1000/spcbox.h ../spcbios/loading.s tap2bin.py
2023-03-17 src/lib/util/options.cpp
2023-03-20 mame/src/devices/bus/spc1000/neo.h spcbios/bootpi.s spcbios/main.c
2023-03-21 mame/link mame/src/devices/bus/spc1000/neo.cpp mame/src/devices/bus/spc1000/spcbox.h mame/src/emu/diimage.h spcbios/bootpi.s spcbios/loading.s spcbios/main.c
2023-03-21 spcbios/loading.s spcbios/main.c
2023-03-25 spc1000.bin
2023-03-30 bin2tap.py
2023-03-30 LISP-SPC1000.tap PHOENIX_all.tap spc1000-lisp.bin
2023-06-12 mame.patch
2024-05-13 Makefile
2024-05-13 Makefile config.h kernel.cpp kernel.h ugui/ugui_config.h
2024-05-14 Makefile index.html main.c
2024-05-16 Makefile config.h kernel.cpp kernel.h kernel.img oscillator.cpp oscillator.h soundrecorder.cpp soundrecorder.h synthmodule.h
2024-05-16 kernel.cpp
2024-05-17 .cproject Makefile include/SDL_config.h include/SDL_config_circle.h src/SDL.c src/audio/SDL_audio.c src/audio/raspberry/SDL_raspberryaudio.c src/core/circle/SDL_circle.c src/core/raspberry/SDL_raspbe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
2024-05-17 diff_0 diff_r
2024-05-17 kernel/.cproject kernel/.gitignore kernel/.project kernel/Makefile kernel/audio.c kernel/audio.h kernel/common.mk kernel/console.c kernel/console.h kernel/emmc.c kernel/emmc.h kernel/fatfs/00readme.t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
2024-05-17 Makefile kernel.cpp kernel.h main.cpp
2024-05-27 kernel.cpp kernel.h
2024-06-02 main.c
2024-06-03 common.h main.c
2024-06-28 MC6847Screen.cpp MC6847Screen.h
2024-07-01 ../baremetal/kernel.cpp ../baremetal/kernel.h ../baremetal/spcall.c ../baremetal/spcall.h ../baremetal/spcall.rom main.cpp
2024-07-02 Makefile main.cpp
2024-07-03 jgz80 sdl2/Makefile sdl2/cpu.cpp sdl2/cpu.h sdl2/main.cpp sdl2/z80.c sdl2/z80.h
2024-07-04 ../jgz80 ay8910.h cassette.h spcall.c spcall.h
2024-07-04 jgz80 sdl2/Makefile sdl2/ay8910.h sdl2/cpu.h sdl2/main.cpp sdl2/mc6847.cpp sdl2/mc6847.h
2024-07-08 ../jgz80 emu2419.c emu2419.h
2024-07-09 ../emu2149 ../jgz80 ay8910.h emu2149.c emu2149.h main.cpp
2024-07-09 ../emu2149 ../jgz80 Makefile cassette.h cpu.h main.cpp
2024-07-09 ../emu2149 ../jgz80 Makefile cassette.cpp cassette.h main.cpp
2024-07-11 ../emu2149 ../jgz80 cassette.cpp cassette.h cpu.h main.cpp spcall.c
2024-07-12 .gitmodules UGUI emu2149 jgz80 sdl2/Makefile sdl2/ay8910.h sdl2/cassette.cpp sdl2/cassette.h sdl2/main.cpp
2024-07-12 ../emu2149 ../jgz80 cassette.cpp cassette.h main.cpp ../tape/tapinfo.c
2024-07-13 bas2txt/bas2txt.py emu2149 jgz80 sdl2/Makefile sdl2/cassette.cpp sdl2/main.cpp tape/3_.tap tape/4_B.tap tape/contest11A.tap tape/spc1000-lisp.bin tape/tapinfo.c tape/tapinfo.py txt2bas/txt2bas.c
2024-07-14 ../emu2149 ../jgz80 main.py
2024-07-15 ../emu2149 ../jgz80 Makefile main.cpp ../tape/taps/15_.tap ../tape/taps/16_.tap ../tape/taps/17_.tap ../tape/taps/18_.tap ../tape/taps/19_.tap ../tape/taps/1_.tap ../tape/taps/22_.tap ../tape/taps/23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
2024-07-16 ../emu2149 ../jgz80 Makefile cassette.cpp keyboard.cpp keyboard.h main.cpp
2024-07-16 ../emu2149 ../jgz80 Makefile cassette.cpp cassette.h index.html main.cpp ../tape/tapbin.py
2024-07-17 ../emu2149 ../jgz80 Makefile cassette.cpp cassette.h emu2149.h index.html main.cpp
2024-07-18 ../emu2149 ../jgz80 keyboard.html
2024-07-19 Makefile index.html keyboard.cpp keyboard.h main.cpp
2024-07-19 typing.wav
2024-07-19 index.html keyboard.cpp keyboard.h
2024-07-21 emu2149 jgz80 sdl2/cassette.cpp sdl2/index.html sdl2/keyboard.cpp sdl2/keyboard.h sdl2/main.cpp
2024-07-22 ../emu2149 ../jgz80 main.cpp
2024-07-22 ../emu2149 ../jgz80 cassette.cpp main.cpp ../spcemul/SPCEMUL.INI ../spcemul/spcmain.cpp ../tape/tapinfo.py
2024-07-24 ../emu2149 ../jgz80 Makefile cassette.cpp cpu.h main.cpp
2024-07-27 ../emu2149 ../jgz80 cassette.cpp cassette.h main.cpp
2024-08-05 bas2txt.py ../emu2149 ../jgz80 ../sdl2/cassette.cpp ../sdl2/main.cpp
2024-08-07 h2png.py
2024-08-08 cassette.cpp
2024-08-09 UGUI emu2149 jgz80 mame/apply_patch mame/backup/scripts/src/bus.lua mame/src/devices/bus/spc1000/miniz.h -> mame/backup/src/devices/bus/spc1000/miniz.h mame/src/devices/bus/spc1000/miniz_common.h -> 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
2024-08-19 heli_adv/HELI_ADV.machine_code.txt heli_adv/HELI_ADV.tap heli_adv/HELI_ADV[M].tap
2024-08-27 ../UGUI Makefile bin/cpmchattr.exe bin/cpmchmod.exe bin/cpmcp.exe bin/cpmls.exe bin/cpmrm.exe bin/fsck.cpm.exe bin/mkfs.cpm.exe bin/putsys2.exe bin/vfd2d88.exe bin/vferase.exe bin/vformat.exe bin/vfr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
2024-08-27 ../UGUI Makefile spc-1000_cpm_boot.inc spc-1000_cpm_boot.lis spc1000.zip ../emu2149 ../jgz80
2024-08-29 ../UGUI mastering_cpm.pdf ../emu2149 ../jgz80
2024-09-06 msxarchive.py
2024-09-06 download_files.py
2024-09-09 web_mirrioring.py
2024-09-09 ../cpm/spc-1000_cpm_boot.asm
2024-09-10 webcopy/download_files.py
2024-09-11 UGUI emu2149 jgz80 webcopy/download_files.py webcopy/web_mirrioring.py
2025-04-04 mame/backup/src/devices/bus/spc1000/neo.cpp
2025-04-10 mame/backup/src/devices/bus/spc1000/Makefile mame/backup/src/devices/bus/spc1000/libinfo.cc mame/backup/src/devices/bus/spc1000/neo.cpp mame/backup/src/devices/bus/spc1000/neo.h mame/backup/src/devic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
2025-04-10 Makefile spcbox.h spcdrive.cc
2025-04-10 make_patch mame.patch.250411
2025-04-11 Makefile neo.cpp neo.h spcbox.h spcdrive.cc
2025-04-11 emu2149 sdl2/emu2149.h
2025-04-11 Makefile raspberry.ld
2025-04-13 UGUI baremetal/Makefile baremetal/kernel.cpp baremetal/kernel.h baremetal/ugui/uguicpp.cpp baremetal/zout/spc-1000_ipl.ams baremetal/zout/spc-1000_ipl.bds baremetal/zout/spc-1000_ipl.cim baremetal/zo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
2025-04-14 Makefile Rules.mk bzip2/bzlib.c bzip2/bzlib_private.h cassette.cpp cassette.h spc1000.cpp spc1000.h ../emu2149 ../mame/backup/src/devices/bus/spc1000/miniz_export.h ../sdl2/ugui.c
2025-04-14 circle/bzip2/bzlib.c circle/cassette.cpp circle/kernel.h circle/miniz/miniz_common.h sdl2/cassette.cpp sdl2/cassette.h
2025-04-14 Keyboard.h kernel.cpp kernel.h
2025-04-14 ../UGUI ../baremetal/ugui/sample/Makefile ../baremetal/ugui/sample/kernel.cpp ../baremetal/ugui/ugui.h ../baremetal/ugui/ugui_config.h ../baremetal/ugui/uguicpp.cpp ../baremetal/ugui/uguicpp.h Keyboa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
2025-04-16 Makefile spcbox.h ../../../../../../spcbox_bm/common.mk ../../../../../../spcbox_bm/main.cpp ../../../../../../spcbox_bm/spcbox.h
2025-04-19 ../UGUI ../circle/kernel.cpp ../circle/kernel.h ../emu2149 ../jgz80 main.cpp pireg.h
2025-04-19 ../UGUI ../emu2149 ../jgz80 spcbox.h
2026-01-14 emu2149.h
2026-01-16 ../emu2149 build_options.conf kernel_extra.config make.sh x86run.sh
2026-01-17 ../emu2149 main.cpp
2026-01-18 ../emu2149 Makefile cassette.h main.cpp
2026-02-17 Makefile cassette.cpp
2026-03-17 baremetal/Makefile baremetal/bin/z80asm baremetal/bmp2c.py baremetal/kernel.cpp baremetal/kernel.h baremetal/main.cpp baremetal/ugui/Makefile baremetal/ugui/ugui_config.h baremetal/ugui/uguicpp.cpp b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
2026-06-25 README.md circle/Rules.mk sdl-wasm/.gitignore sdl-wasm/MC6847.c sdl-wasm/Makefile sdl2/Makefile sdl2/ay8910.h sdl2/cassette.cpp sdl2/hangul-dkby-dinaru-2.png sdl2/hangul-dkby-dinaru-2.png.h sdl2/main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
2026-06-27 Fix WASM runtime crashes (stack/table overflow) and correct MC6847 color channel alignment
2026-06-30 Makefile z80asm.exe
2026-06-30 Fix baremetal boot hang, Z80 timer interrupts, sound_mutex pointer bug, and complete 32KB ROM
2026-06-30 Fix BSS overlap: Move large tape buffer in Cassette class from static BSS to heap allocation
